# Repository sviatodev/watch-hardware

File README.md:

# OLED Bluetooth 4.0 Watch
  - STM32L151 MCU with 128k Flash and 16k RAM
  - Bluetooth 4.0 HC-08 tranceiver
  - Piezoelectric buzzer
  - Vibration motor
  - Battery charging circuit
  - 3 buttons
  - BME280 weather sensor (temperature, pressure, humidity)
  - BMC150 3-axis accelerometer and 3-axis compass
  - OLED monochrome 128x64 I2C LCD
  - Micro USB socket (USB 3.0 socket part used for programmer SWD pins)
  - Socket for STM32F3Discovery ST-Link header (can be cut-off)

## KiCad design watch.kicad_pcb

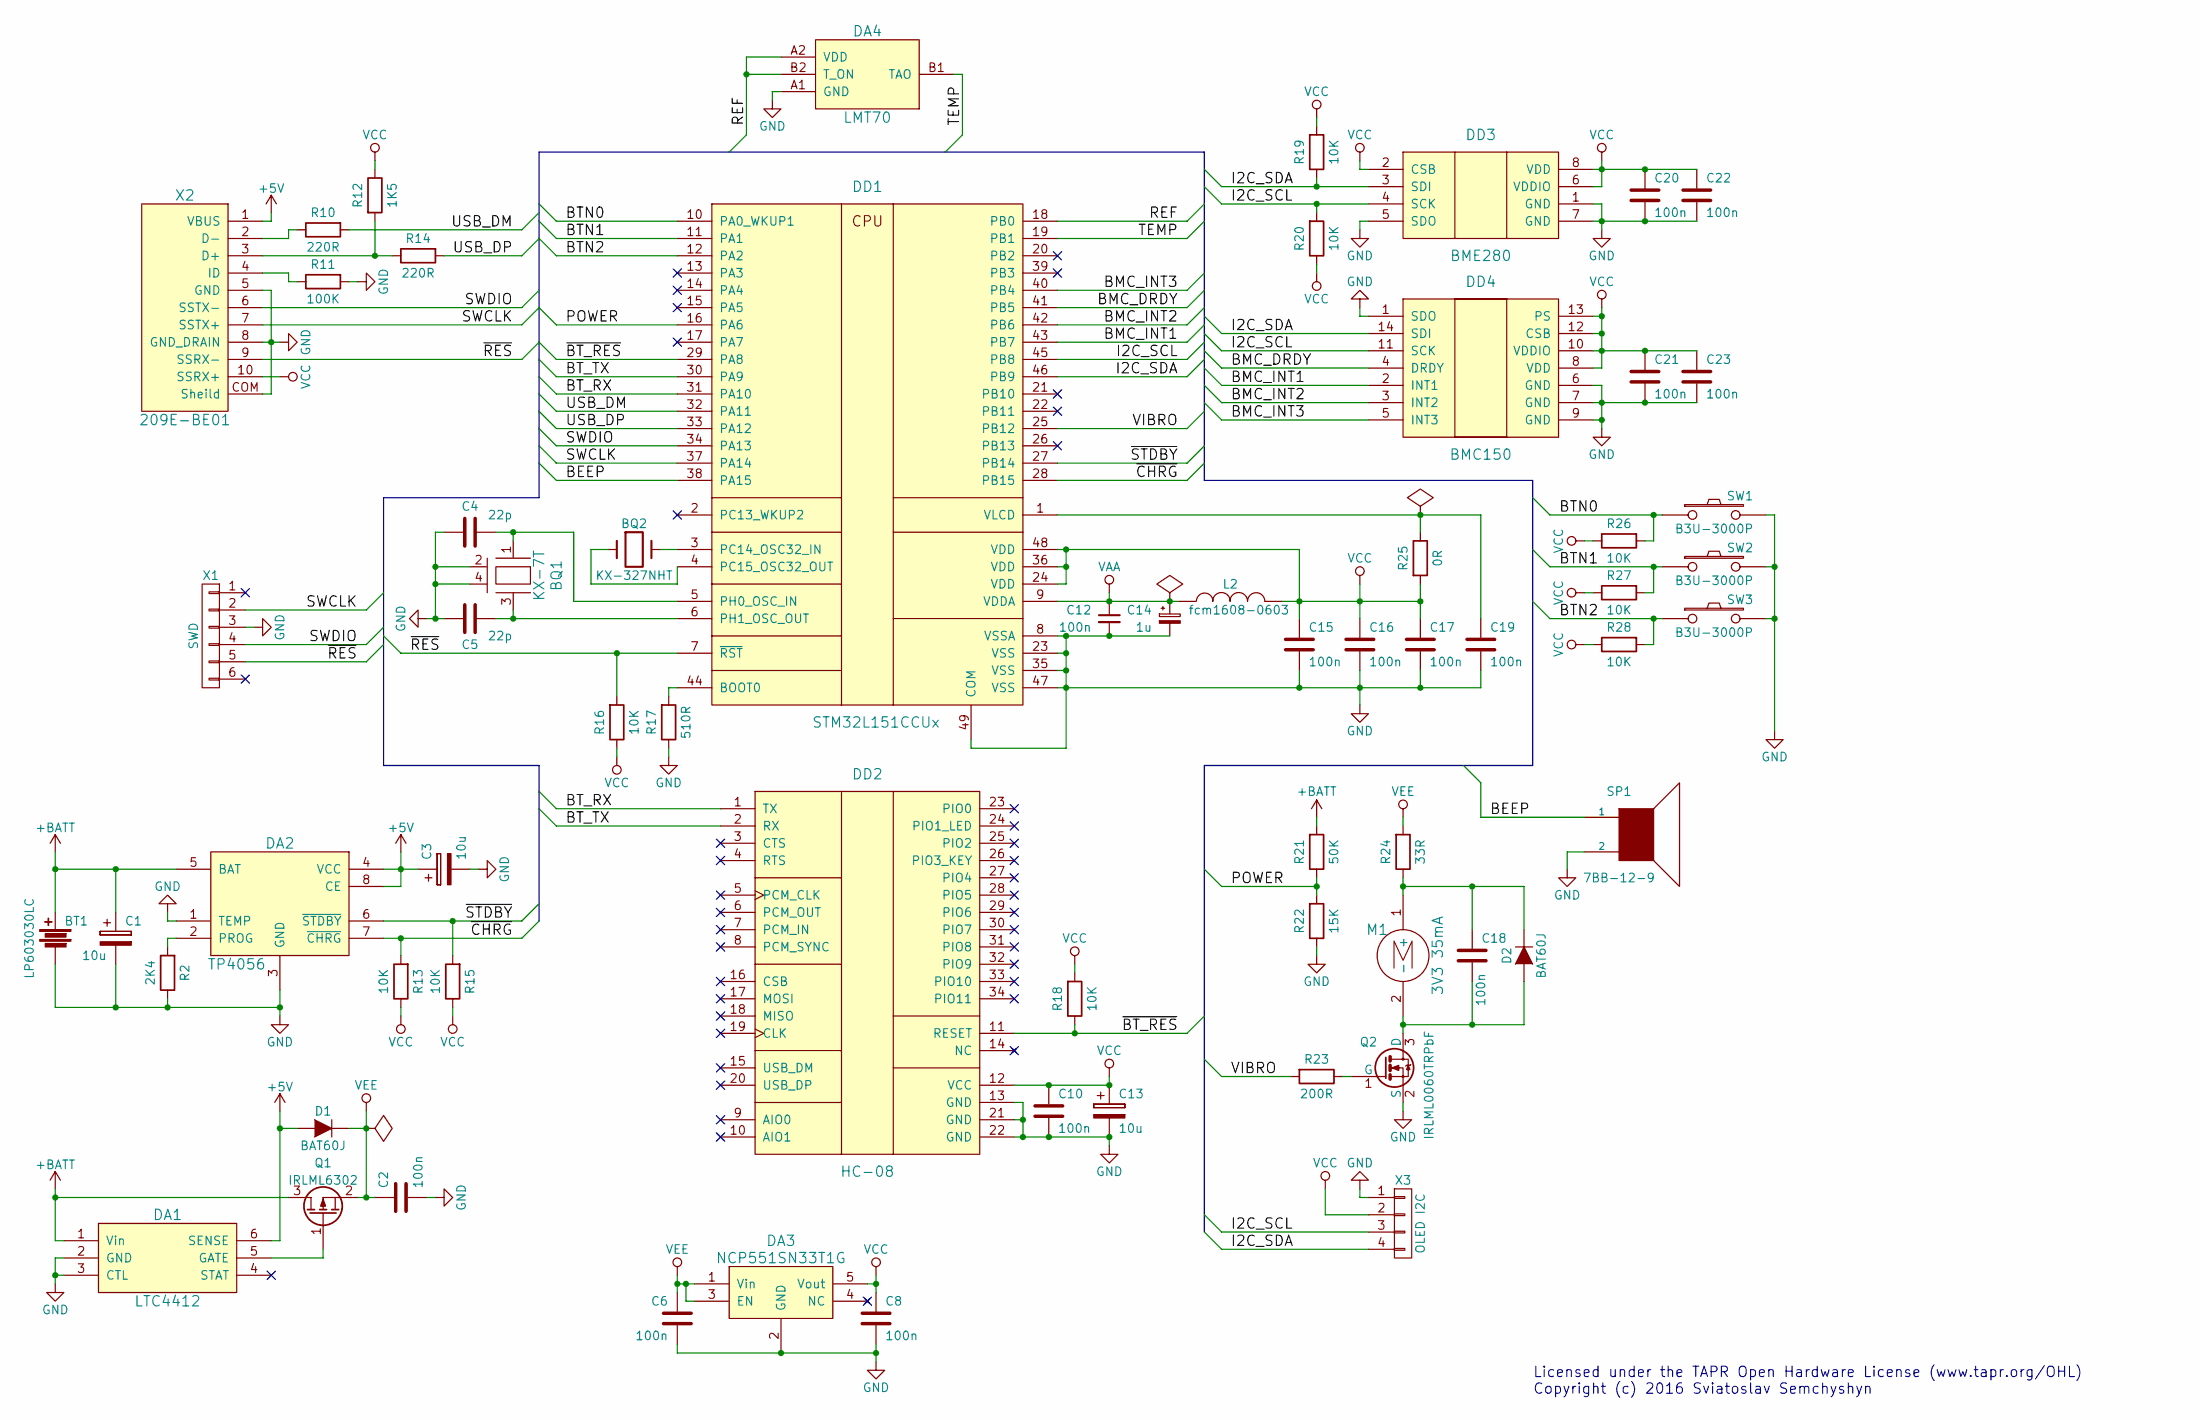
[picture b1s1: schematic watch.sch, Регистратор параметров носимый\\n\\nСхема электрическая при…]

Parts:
BQ1: KX-7T
BQ2: KX-327NHT
BT1: LP603030LC; R_0805_HandSoldering
C1, C3, C13: 10u; C_0805
C2, C6, C8, C10, C12, C15, C16, C17, C18, C19, C20, C21, C22, C23: 100n; C_0402
C4, C5: 22p; C_0402
C14: 1u; C_0603
D1, D2: BAT60J; SOD-323
DA1: LTC4412; SOT-23-6
DA2: TP4056; SOP-8
DA3: NCP551SN33T1G; SOT-23-5
DA4: LMT70; DSBGA4
DD1: STM32L151CCUx; QFN-48-1EP_7x7mm_Pitch0.5mm
DD2: HC-08
DD3: BME280
DD4: BMC150
L2: fcm1608-0603; R_0603
M1: 3V3 35mA; R_0805_HandSoldering
Q1: IRLML6302; SOT-23
Q2: IRLML0060TRPbF; SOT-23
R2: 2K4; R_0402
R10, R14: 220R; R_0402
R11: 100K; R_0402
R12: 1K5; R_0402
R13, R15, R16, R18, R19, R20, R26, R27, R28: 10K; R_0402
R17: 510R; R_0402
R21: 50K; R_0402
R22: 15K; R_0402
R23: 200R; R_0402
R24: 33R; R_0402
R25: 0R; R_0402
SP1: 7BB-12-9; R_0805_HandSoldering
SW1, SW2, SW3: B3U-3000P
X1: SWD; Pin_Header_Straight_1x06
X2: 209E-BE01
X3: OLED I2C; Pin_Header_Straight_1x04

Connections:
+5V: C3.1, D1.2 (A), DA1.6 (SENSE), DA2.4 (VCC), DA2.8 (CE), X2.1 (VBUS)
+BATT: BT1.1, C1.1, DA1.1 (Vin), DA2.5 (BAT), Q1.3 (D), R21.2
/BEEP: DD1.38 (PA15), SP1.1
/BMC_DRDY: DD1.41 (PB5), DD4.4 (DRDY)
/BMC_INT1: DD1.43 (PB7), DD4.2 (INT1)
/BMC_INT2: DD1.42 (PB6), DD4.3 (INT2)
/BMC_INT3: DD1.40 (PB4), DD4.5 (INT3)
/BTN0: DD1.10 (PA0_WKUP1), R26.2, SW1.1
/BTN1: DD1.11 (PA1), R27.2, SW2.1
/BTN2: DD1.12 (PA2), R28.2, SW3.1
/BT_RX: DD1.31 (PA10), DD2.1 (TX)
/BT_TX: DD1.30 (PA9), DD2.2 (RX)
/I2C_SCL: DD1.45 (PB8), DD3.4 (SCK), DD4.11 (SCK), R20.2, X3.3
/I2C_SDA: DD1.46 (PB9), DD3.3 (SDI), DD4.14 (SDI), R19.1, X3.4
/POWER: DD1.16 (PA6), R21.1, R22.2
/REF: DA4.A2 (VDD), DA4.B2 (T_ON), DD1.18 (PB0)
/SWCLK: DD1.37 (PA14), X1.2, X2.7 (SSTX+)
/SWDIO: DD1.34 (PA13), X1.4, X2.6 (SSTX-)
/TEMP: DA4.B1 (TAO), DD1.19 (PB1)
/USB_DM: DD1.32 (PA11), R10.2
/USB_DP: DD1.33 (PA12), R14.2
/VIBRO: DD1.25 (PB12), R23.2
/~BT_RES: DD1.29 (PA8), DD2.11 (RESET), R18.1
/~CHRG: DA2.7 (~CHRG), DD1.28 (PB15), R13.2
/~RES: DD1.7 (~RST), R16.2, X1.5, X2.9 (SSRX-)
/~STDBY: DA2.6 (~STDBY), DD1.27 (PB14), R15.2
GND: BQ1.2, BQ1.4, BT1.2, C1.2, C2.2, C3.2, C4.2, C5.2, C6.2, C8.2, C10.2, C12.2, C13.2, C14.2, C15.2, C16.2, C17.2, C19.2, C20.2, C21.2, C22.2, C23.2, DA1.2 (GND), DA1.3 (CTL), DA2.1 (TEMP), DA2.3 (GND), DA3.2 (GND), DA4.A1 (GND), DD1.8 (VSSA), DD1.23 (VSS), DD1.35 (VSS), DD1.47 (VSS), DD1.49 (COM), DD2.13 (GND), DD2.21 (GND), DD2.22 (GND), DD3.1 (GND), DD3.5 (SDO), DD3.7 (GND), DD4.1 (SDO), DD4.6 (GND), DD4.7 (GND), DD4.9 (GND), Q2.2 (S), R2.1, R11.2, R17.1, R22.1, SP1.2, SW1.2, SW2.2, SW3.2, X1.3, X2.5 (GND), X2.8 (GND_DRAIN), X2.COM (Sheild), X3.1
unnamed: BQ1.1, C4.1, DD1.5 (PH0_OSC_IN)
unnamed: BQ1.3, C5.1, DD1.6 (PH1_OSC_OUT)
unnamed: BQ2.1, DD1.4 (PC15_OSC32_OUT)
unnamed: BQ2.2, DD1.3 (PC14_OSC32_IN)
unnamed: C18.1, D2.1 (K), M1.1 (+), R24.1
unnamed: C18.2, D2.2 (A), M1.2 (-), Q2.3 (D)
unnamed: C19.1, DD1.1 (VLCD), R25.1
unnamed: DA1.5 (GATE), Q1.1 (G)
unnamed: DA2.2 (PROG), R2.2
unnamed: DD1.44 (BOOT0), R17.2
unnamed: Q2.1 (G), R23.1
unnamed: R10.1, X2.2 (D-)
unnamed: R11.1, X2.4 (ID)
unnamed: R12.2, R14.1, X2.3 (D+)
VAA: C12.1, C14.1, DD1.9 (VDDA), L2.1
VCC: C8.1, C10.1, C13.1, C15.1, C16.1, C17.1, C20.1, C21.1, C22.1, C23.1, DA3.5 (Vout), DD1.24 (VDD), DD1.36 (VDD), DD1.48 (VDD), DD2.12 (VCC), DD3.2 (CSB), DD3.6 (VDDIO), DD3.8 (VDD), DD4.8 (VDD), DD4.10 (VDDIO), DD4.12 (CSB), DD4.13 (PS), L2.2, R12.1, R13.1, R15.1, R16.1, R18.2, R19.2, R20.1, R25.2, R26.1, R27.1, R28.1, X2.10 (SSRX+), X3.2
VEE: C2.1, C6.1, D1.1 (K), DA3.1 (Vin), DA3.3 (EN), Q1.2 (S), R24.2

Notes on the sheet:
Licensed under the TAPR Open Hardware License (www.tapr.org/OHL) Copyright (c) 2016 Sviatoslav Semchyshyn

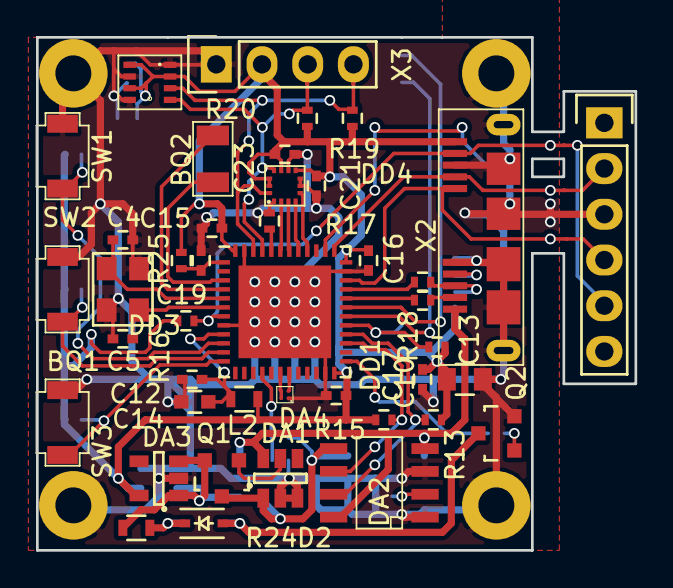
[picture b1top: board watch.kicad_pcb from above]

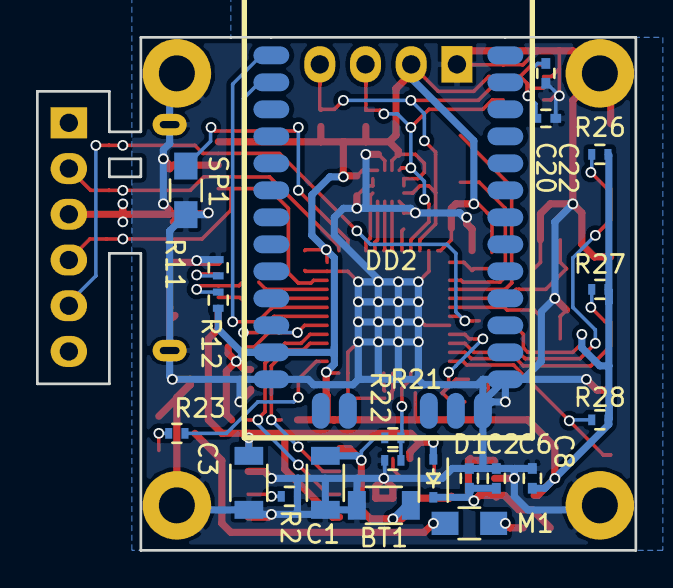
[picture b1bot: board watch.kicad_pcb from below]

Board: 2 copper layers, 33.2 x 28.5 mm, 63 parts (21 on the bottom side), 44 nets.

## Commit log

2016-04-02 Update LICENSE
    Switch project to TAPR Open Hardware License
2016-04-02 Added files via upload
2016-04-02 PCB Changed
2016-04-03 PCB finished, some changes in schematic
2016-04-03 Some small PCB changes
2016-04-03 Add preview images
2016-04-04 Some small changes
2016-04-04 Modified libraries path
2016-04-04 Paths changed
2016-04-04 Add flash connector for stm32f3discovery stlink
2016-04-21 Fixed MCU footprint
2016-05-16 Add photo of real board
